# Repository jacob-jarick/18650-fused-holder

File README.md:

# 5p 18650 Holder

Designed with the goal of a long life time of usage with very easy maintenance and servicing.

# Features
- 10x10cm PCB (cheap).
- per cell fusing using 5x20mm Glass Fuses
- blown fuse indicator LEDs
- m4 mounting pads.

I will be using these to build my power walls.

## BoM Est

$4.50 aud

# Notes

## Bus Bar

I plan to use copper pipe 1/2 inch.

## Attachment to bus bar

copper rivets is the cheapeast option, best option is nutserts and m4 bolts.

## Connecting multiple boards.

using a 2p 18650 case you can join two boards together by placing the 2p case over the end cell spots (eg cell 4 on board 1 and cell 1 on board 2).

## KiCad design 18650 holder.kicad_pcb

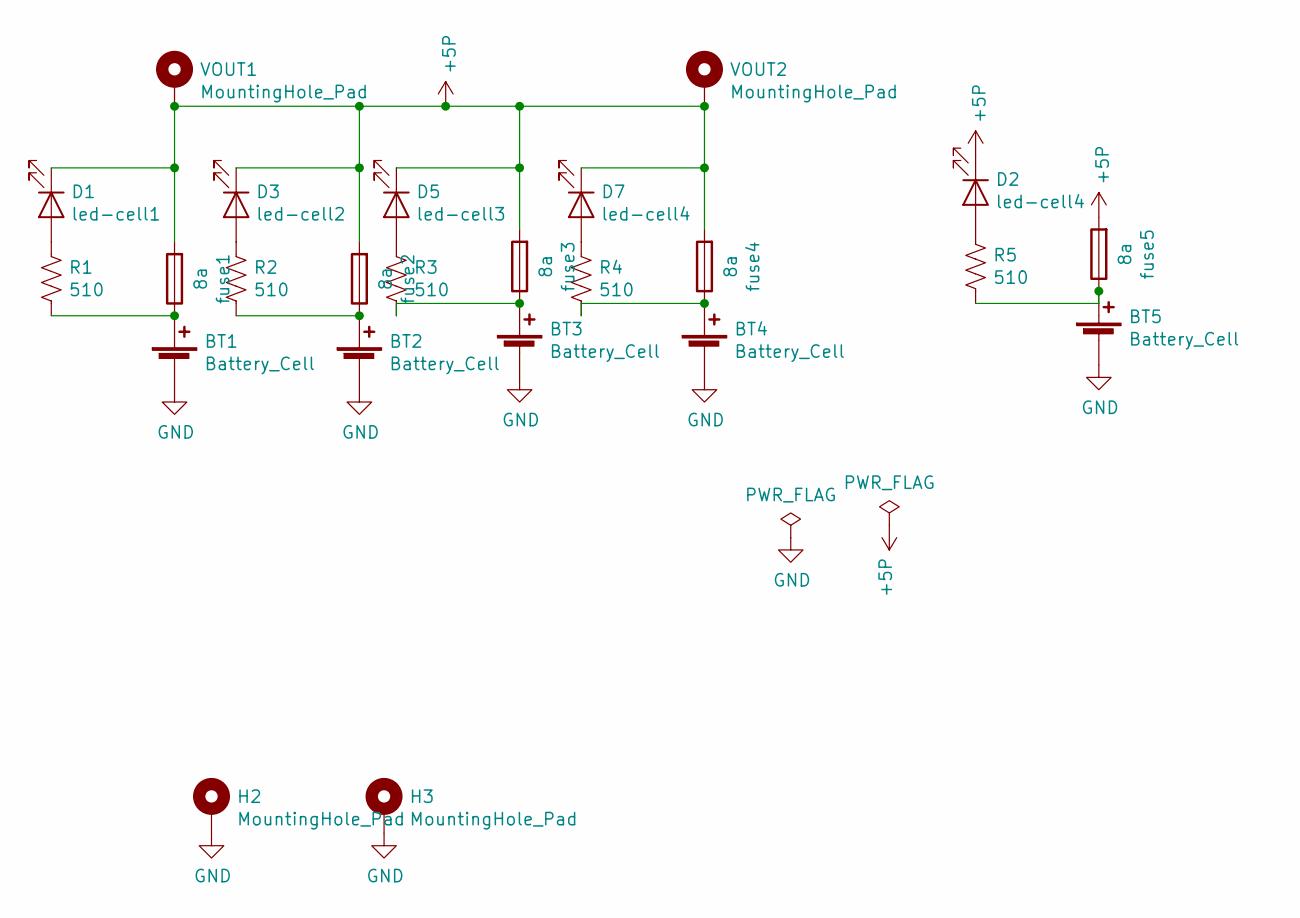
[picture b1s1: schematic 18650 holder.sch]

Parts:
BT1, BT2, BT3, BT4, BT5: Battery_Cell; BatteryHolder_MPD_BH-18650-PC2
D1: led-cell1; LED_1206_3216Metric-witharrow
D2, D7: led-cell4; LED_1206_3216Metric-witharrow
D3: led-cell2; LED_1206_3216Metric-witharrow
D5: led-cell3; LED_1206_3216Metric-witharrow
H2, H3: MountingHole_Pad; MountingHole_4.3x6.2mm_M4_Pad_Via
R1, R2, R3, R4, R5: 510; R_0805_2012Metric_Pad1.15x1.40mm_HandSolder
VOUT1, VOUT2: MountingHole_Pad; MountingHole_4.3x6.2mm_M4_Pad_Via
fuse1, fuse2, fuse3, fuse4, fuse5: 8a; Fuseholder_Cylinder-5x20mm_Schurter_0031_8201_Horizontal_Op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

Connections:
+5P: D1.1 (K), D2.1 (K), D3.1 (K), D5.1 (K), D7.1 (K), VOUT1.1, VOUT2.1, fuse1.2, fuse2.2, fuse3.2, fuse4.2, fuse5.2
GND: BT1.2 (-), BT2.2 (-), BT3.2 (-), BT4.2 (-), BT5.2 (-), H2.1, H3.1
unnamed: BT1.1 (+), R1.2, fuse1.1
unnamed: BT2.1 (+), R2.2, fuse2.1
unnamed: BT3.1 (+), R3.2, fuse3.1
unnamed: BT4.1 (+), R4.2, fuse4.1
unnamed: BT5.1 (+), R5.2, fuse5.1
unnamed: D1.2 (A), R1.1
unnamed: D2.2 (A), R5.1
unnamed: D3.2 (A), R2.1
unnamed: D5.2 (A), R3.1
unnamed: D7.2 (A), R4.1

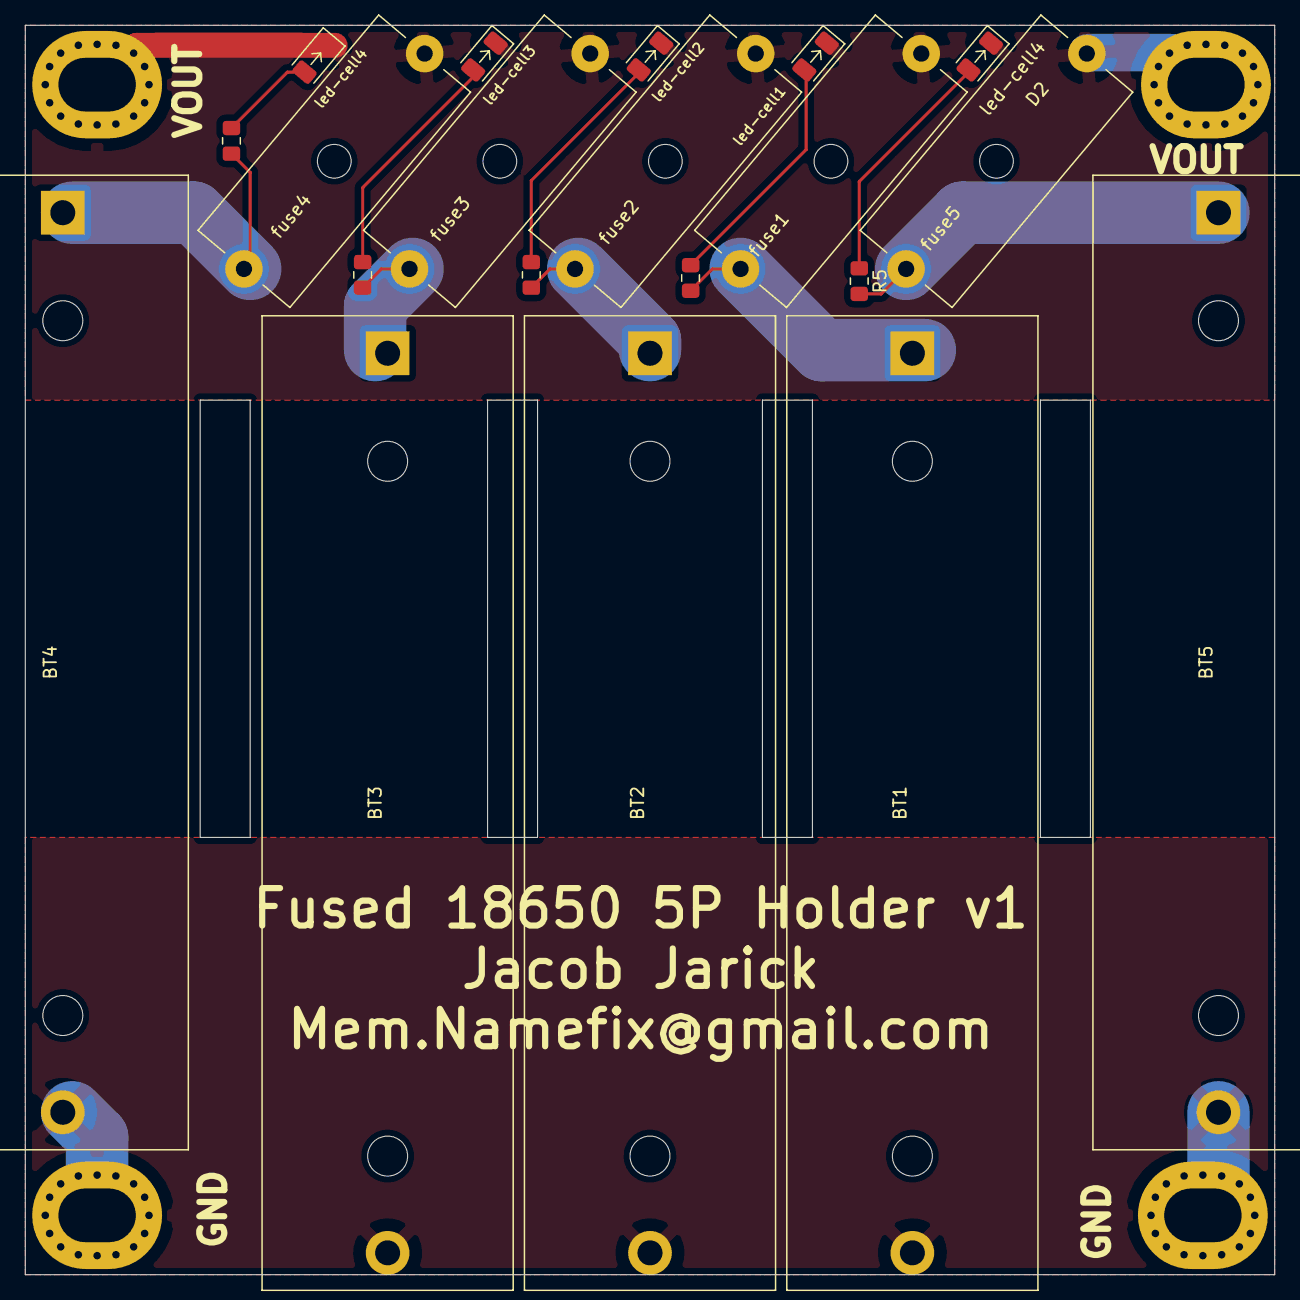
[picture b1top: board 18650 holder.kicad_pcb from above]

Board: 2 copper layers, 100.0 x 100.0 mm, 24 parts (0 on the bottom side), 12 nets.

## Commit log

2019-10-08 1st commit
2019-10-08 readme
2019-10-08 rename
